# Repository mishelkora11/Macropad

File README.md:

Macropad:

Demo:

(https://jumpshare.com/share/NGJ5itXQeFNpmC4G9I8h)

3D look of the assembled macropad:

3D look of the macropad wihtout the top attached. PCB view:

Schematic:

PCB:

PCB 3D view:

Case:

Firmware:

The micropad uses QMK Firmware.

Description:

A custom handwired 10-key macropad running QMK firmware on a Seeed Studio XIAO RP2040 development board. 

* Keyboard Maintainer: [mishelkora11](https://github.com/mishelkora11)
* Hardware Supported: Seeed Studio XIAO RP2040, MX-style switches, and an 0.91 inch OLED Display.

BOM:

1x seeed studio rp2040

4x  style switches

1x 0.91 inch oled display

4x M3x5x4 Heatset inserts

1x Case 

4x M3x16mm screws

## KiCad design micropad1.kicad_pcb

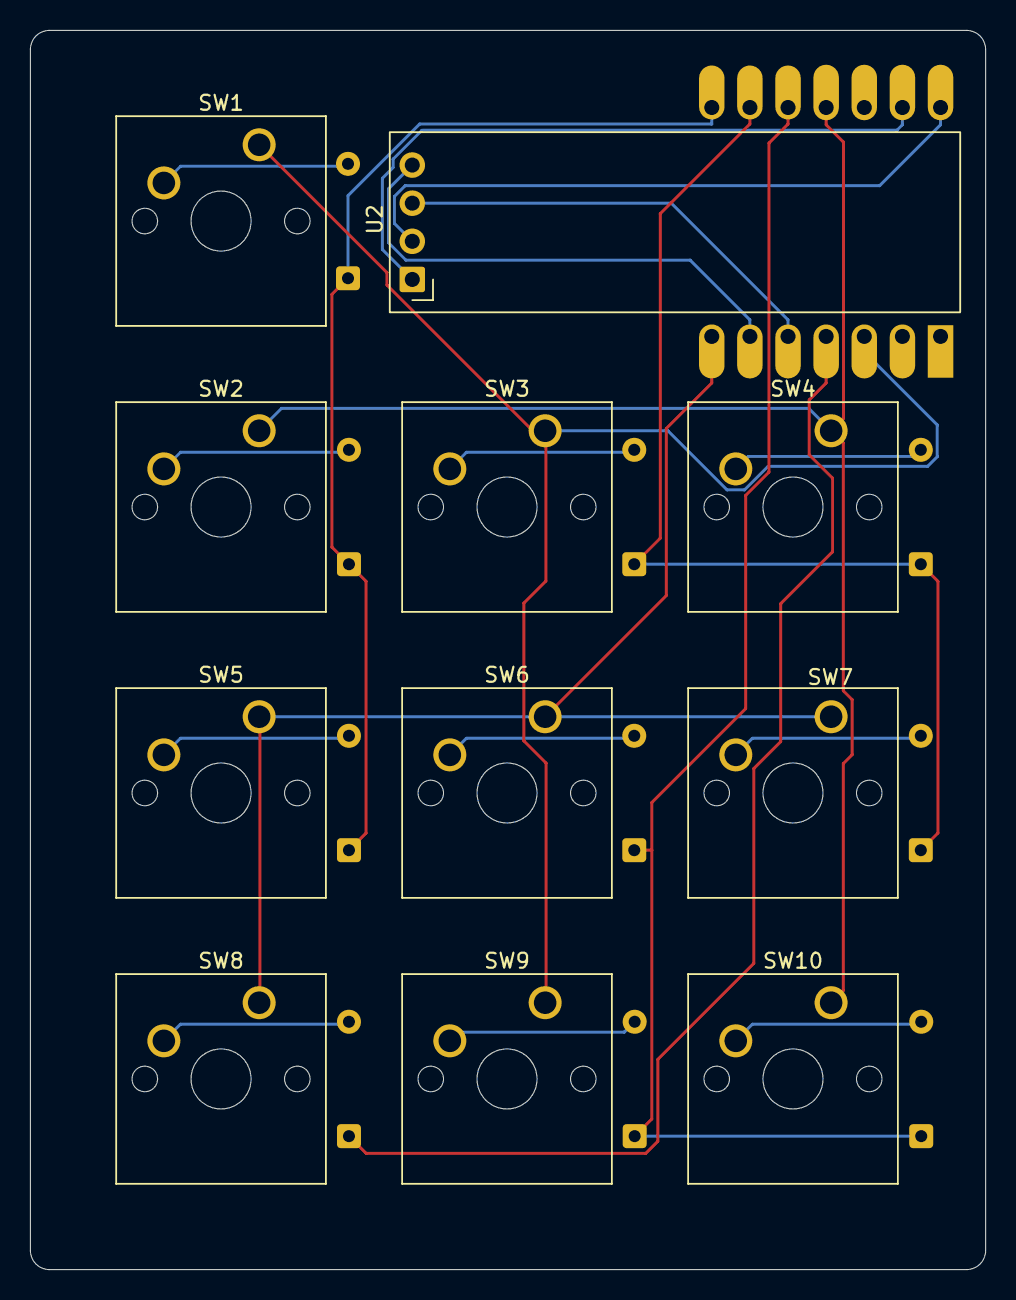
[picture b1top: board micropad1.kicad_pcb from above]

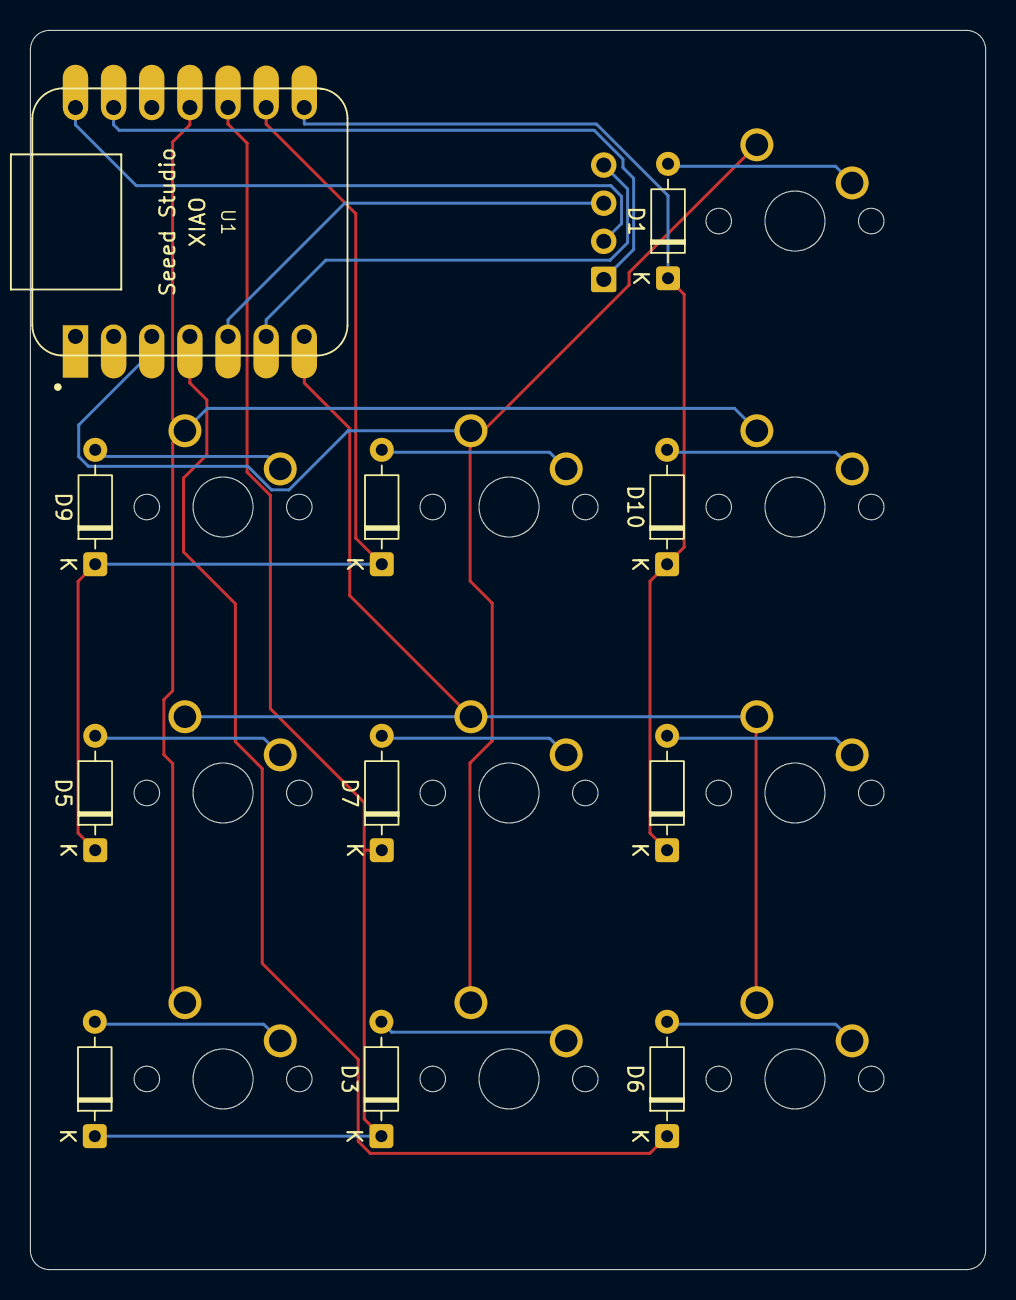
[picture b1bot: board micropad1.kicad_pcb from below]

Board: 2 copper layers, 63.6 x 82.6 mm, 22 parts (11 on the bottom side), 21 nets.

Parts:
D1, D2, D3, D4, D5, D6, D7, D8, D9, D10: 1N4148; D_DO-35_SOD27_P7.62mm_Horizontal
SW1, SW2, SW3, SW4, SW5, SW6, SW7, SW8, SW9, SW10: SW_Push; SW_Cherry_MX_1.00u_PCB
U1: MOUDLE-SEEEDUINO-XIAO; XIAO-Generic-Hybrid-14P-2.54-21X17.8MM
U2: ER_OLEDM0.91_1x-I2C

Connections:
Column 0: SW5.1, SW6.1, SW7.1, SW8.1, U1.7 (PB08_A6_D6_TX)
Column 1: SW1.1, SW3.1, SW9.1, U1.3 (PA10_A2_D2)
Column 2: SW2.1, SW4.1, SW10.1, U1.11 (PA6_A10_D10_MOSI)
unnamed: D1.2 (A), SW1.2
unnamed: D2.2 (A), SW3.2
unnamed: D3.2 (A), SW9.2
unnamed: D4.2 (A), SW5.2
unnamed: D5.2 (A), SW7.2
unnamed: D6.2 (A), SW8.2
unnamed: D7.2 (A), SW6.2
unnamed: D8.2 (A), SW10.2
unnamed: D9.2 (A), SW4.2
unnamed: D10.2 (A), SW2.2
unnamed: U1.14 (5V), U2.2 (VCC)
unnamed: U1.13 (GND), U2.1 (GND)
unnamed: U1.5 (PA8_A4_D4_SDA), U2.3 (SCL)
unnamed: U1.6 (PA9_A5_D5_SCL), U2.4 (SDA)
Row 0: D6.1 (K), U1.4 (PA11_A3_D3)
Row 1: D1.1 (K), D4.1 (K), D10.1 (K), U1.8 (PB09_A7_D7_RX)
Row 2: D2.1 (K), D5.1 (K), D9.1 (K), U1.9 (PA7_A8_D8_SCK)
Row 3: D3.1 (K), D7.1 (K), D8.1 (K), U1.10 (PA5_A9_D9_MISO)
